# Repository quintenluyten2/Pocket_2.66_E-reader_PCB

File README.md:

# Pocket 2.66 — E-reader PCB

A compact e-reader PCB built around a 2.13"/2.66" e-ink display and the ESP32-C3FH4 microcontroller.

## Features

- **MCU:** ESP32-C3FH4 (RISC-V, 2.4 GHz Wi-Fi + BLE, 4 MB flash)
- **Display:** 2.13"/2.66" e-ink, connected via 24-pin FPC
- **Power:** USB-C input, single-cell Li-Po with GX4054 charger and BQ27220 fuel gauge
- **Storage:** micro-SD card slot
- **Connectivity:** On-board SMD 2.4 GHz antenna (Not yet matched to 35 Ohm)
- **Form factor:** 4-layer 1 mm PCB, min trace 0.12 mm, min via 0.3/0.4 mm (designed for JLCPCB)

## Repository contents

```
├── Pocket 2.66.kicad_sch       Schematic
├── Pocket 2.66.kicad_pcb       PCB layout
├── Pocket 2.66.kicad_pro       KiCad project file
├── Pocket 2.66.kicad_dru       Design rules
├── libs/lcsc/.                 Component Library
├── documentation/
│   ├── Pocket 2.66 BOM with MPN.csv   Schematic BOM
│   ├── Pocket 2.66 Interactive.html   Interactive PCB BOM
│   ├── PCB.stl
│   └── V0_schematic_review.pdf
└── production/
    ├── Pocket_2.66.zip         Gerber + drill files for fabrication
    ├── bom.csv                 JLCPCB BOM (for PCBA)
    ├── positions.csv           JLCPCB pick-and-place (for PCBA)
    └── netlist.ipc
```

## Additional parts
To make an E-reader, you need this PCB fully assembled, and:
- **Display** 24-pin 2.13"/2.66" Black/White E-ink display (e.g. Waveshare)
- **Battery** 803450 1500 mAh battery for 2.66" version or 802540 800 mAh battery for 2.13" version. Use 1.25 mm 2P Picoblade connector
- **Housing** 3D printing files coming soon

## Key components

| Ref | Part | Description |
|-----|------|-------------|
| U1 | ESP32-C3FH4 | Main MCU |
| U2 | LCK-TF-027H30008-WLG | Push-pull micro-SD slot |
| U3 | GX4054 | Li-Po charger |
| U4 | GS2019-33TR5 | 3.3 V LDO |
| U5 | BQ27220YZFR | Battery fuel gauge |
| U6 | SRV05-4-P-T7 | USB ESD protection |
| P1 | USB-TYPE-C-018 | USB-C connector |
| P3 | FPC-05F-24PH20 | 24-pin FPC for e-ink display |
| ANT2 | H2U38D1E1B0100 | 2.4 GHz SMD antenna |
| X1 | XL7EL89CLI-111YLC-40M | 40 MHz crystal |

## Opening the project

1. Open **KiCad 8** or later.
2. File → Open Project → select `Pocket 2.66.kicad_pro`.
3. The component library is self-contained in `libs/lcsc/`. The project's `fp-lib-table` and `sym-lib-table` already point to it, so no additional setup is needed.
4. Set the `KICAD_LCSC_3D_MODEL_DIR` path variable to `${KIPRJMOD}/libs/lcsc/3dmodels` for 3D models to appear (Preferences → Configure Paths).

## Production files

Ready-to-order Gerber files are in `production/Pocket_2.66.zip`. The BOM and pick-and-place files are formatted for JLCPCB PCBA.

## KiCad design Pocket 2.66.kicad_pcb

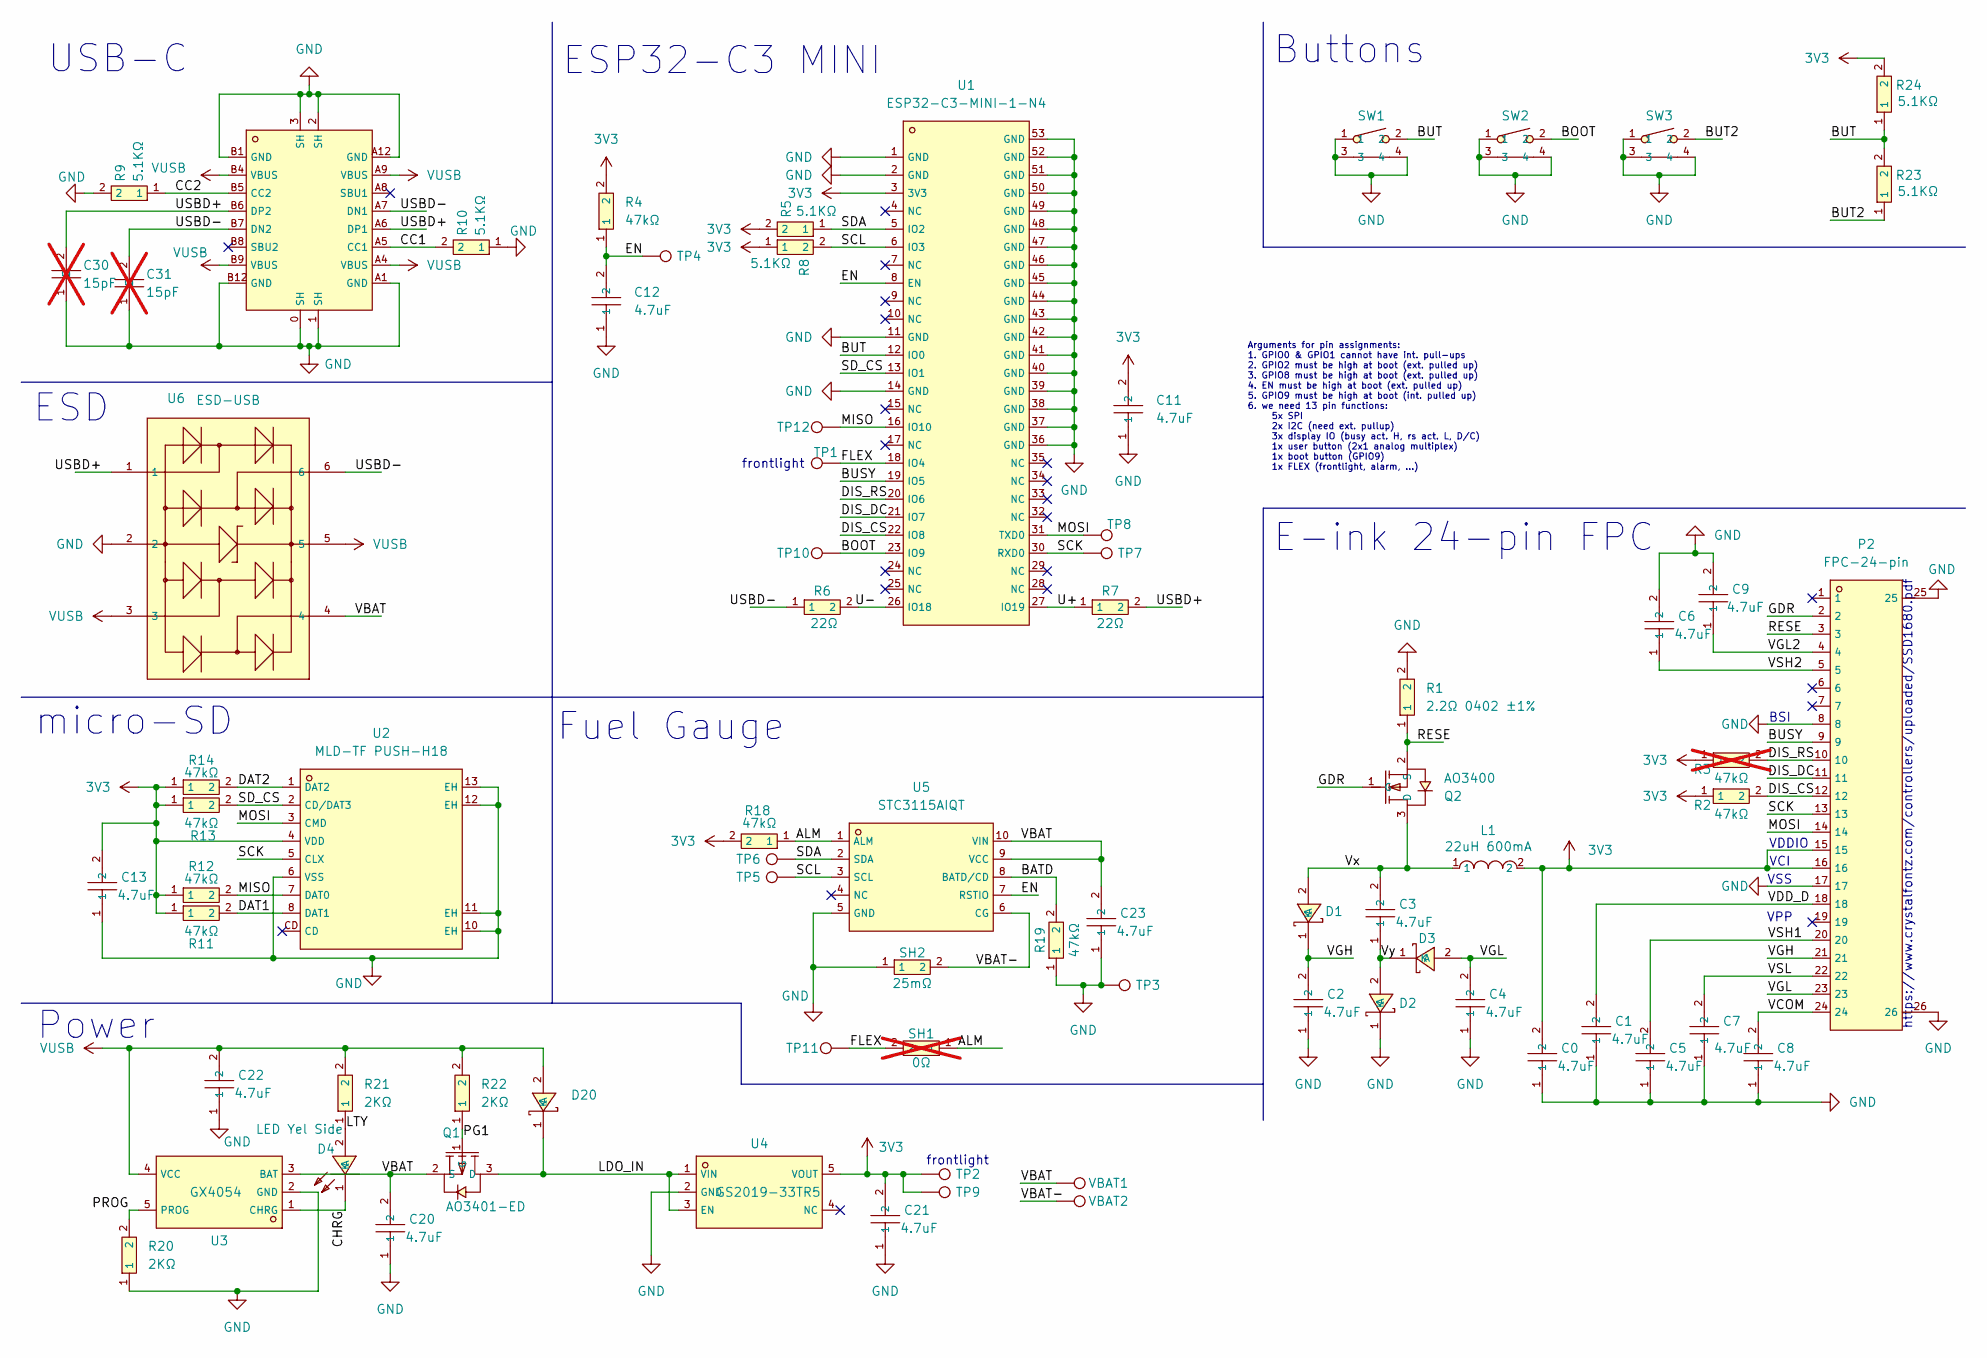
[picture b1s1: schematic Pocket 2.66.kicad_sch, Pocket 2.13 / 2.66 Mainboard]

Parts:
C0, C1, C2, C3, C4, C5, C6, C7, C8, C9, C11, C12, C13, C20, C21, C22, C23: 4.7uF; C0402; MPN CGA0402X5R475M250GT; LCSC C6119795
C30, C31: 15pF; C0402; MPN 0402CG150J500NT; LCSC C1548; not fitted
D1, D2, D3, D20: SD103AWS-L SOD-323; C191023_SOD-323_L1_8-W1_3-LS2_5-RD; MPN SD103AWS-L; LCSC C41376466
D4: LED Yel Side; C52675985_LED_Side; MPN CT-1706UYC-P11; LCSC C52675985
L1: 22uH 600mA; C48689518_L1008; MPN SRTC.252010.YB220MT00; LCSC C48689518
P1: TYPE-C 16P CB1.6 073; C2906290_USB-C-SMD_SHOU_TYPE-C-16P-CB1_6; MPN TYPE-C 16P CB1.6 073; LCSC C2906290
P2: FPC-24-pin; C324726_FFC-SMD_24P-P0_50_FH34SRJ-24S-0_5SH; MPN FH34SRJ-24S-0.5SH(50); LCSC C324726
Q1: AO3401-ED; SOT23-3; MPN AO3401-ED; LCSC C4748724
Q2: AO3400; SOT-23-L; MPN AO3400; LCSC C20634976
R1: 2.2Ω 0402 ±1%; R0402; MPN FRC0402F2R20TS; LCSC C2909330
R2, R4, R11, R12, R13, R14, R18, R19: 47kΩ; R0402; MPN FRC0402F4702TS; LCSC C2906872
R3: 47kΩ; R0402; MPN FRC0402F4702TS; LCSC C2906872; not fitted
R5, R8, R9, R10, R23, R24: 5.1KΩ; R0402; MPN 0402WGF5101TCE; LCSC C25905
R6, R7: 22Ω; R0402; MPN RC0402FR-0722RL; LCSC C114765
R20, R21, R22: 2KΩ; R0402; MPN 0402WGF2001TCE; LCSC C4109
SH1: 0Ω; R0402; not fitted
SH2: 25mΩ; R0603; MPN RL0603FR-070R025L; LCSC C859739
SW1, SW2, SW3: TS-24CA-S16; C42420265_SW-SMD_L4_7-W3_5-P3_35-EH; MPN TS-24CA-S16; LCSC C42420258
TP1, TP2: TestPoint; TestPoint_Pad_D1.5mm
TP3, TP4, TP5, TP6, TP7, TP8, TP9, TP10, TP11, TP12: TestPoint; TestPoint_Pad_D1.0mm
U1: ESP32-C3-MINI-1-N4; C2838502_WIFIM-SMD_ESP32-C3-MINI-1; LCSC C2838502
U2: MLD-TF PUSH-H18; C52750848_SD-SMD_MLD-TF-PUSH-H18; LCSC C52750848
U3: GX4054; SOT-23-5; MPN GX4054; LCSC C5259235
U4: GS2019-33TR5; SOT-23-5; MPN GS2019-33TR5; LCSC C41419378
U5: STC3115AIQT; C2688637_DFN-10_L3_0-W2_0-P0_50-BL; MPN STC3115AIQT; LCSC C2688637
U6: ESD-USB; C85364_SOT-23-6_L2_9-W1_6-P0_95-LS2_8-BR; MPN SRV05-4-P-T7; LCSC C85364
VBAT1, VBAT2: TestPoint; TestPoint_Pad_D1.0mm

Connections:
3V3: C0.2, C11.2, C13.2, C21.2, L1.2, P2.15, P2.16, R2.1, R3.1, R4.2, R5.2, R8.1, R11.1, R12.1, R13.1, R14.1, R18.2, R24.2, TP2.1 (1_1), TP9.1 (1_1), U1.3 (3V3), U2.4 (VDD), U4.5 (VOUT)
/ALM: R18.1, SH1.1, U5.1 (ALM)
/BATD: R19.2, U5.8 (BATD/CD)
/BOOT: SW2.2, TP10.1 (1_1), U1.23 (IO9)
/BUSY: P2.9, U1.19 (IO5)
/BUT: R23.2, R24.1, SW1.2, U1.12 (IO0)
/BUT2: R23.1, SW3.2
/CC1: P1.A5 (CC1), R10.2
/CC2: P1.B5 (CC2), R9.1
/CHRG: D4.1 (K), U3.1 (CHRG)
/DAT1: R11.2, U2.8 (DAT1)
/DAT2: R14.2, U2.1 (DAT2)
/DIS_CS: P2.12, R2.2, U1.22 (IO8)
/DIS_DC: P2.11, U1.21 (IO7)
/DIS_RS: P2.10, R3.2, U1.20 (IO6)
/EN: C12.2, R4.1, TP4.1 (1_1), U1.8 (EN), U5.7 (RSTIO)
/FLEX: SH1.2, TP1.1 (1_1), TP11.1 (1_1), U1.18 (IO4)
/GDR: P2.2, Q2.1 (G)
/LDO_IN: D20.1 (K), Q1.3 (D), U4.1 (VIN), U4.3 (EN)
/LTY: D4.2 (A), R21.1
/MISO: R12.2, TP12.1 (1_1), U1.16 (IO10), U2.7 (DAT0)
/MOSI: P2.14, TP8.1 (1_1), U1.31 (TXD0), U2.3 (CMD)
/PG1: Q1.1 (G), R22.1
/PROG: R20.2, U3.5 (PROG)
/RESE: P2.3, Q2.2 (S), R1.1
/SCK: P2.13, TP7.1 (1_1), U1.30 (RXD0), U2.5 (CLX)
/SCL: R8.2, TP5.1 (1_1), U1.6 (IO3), U5.3 (SCL)
/SDA: R5.1, TP6.1 (1_1), U1.5 (IO2), U5.2 (SDA)
/SD_CS: R13.2, U1.13 (IO1), U2.2 (CD/DAT3)
/U+: R7.1, U1.27 (IO19)
/U-: R6.2, U1.26 (IO18)
/USBD+: C30.2, P1.A6 (DP1), P1.B6 (DP2), R7.2, U6.1
/USBD-: C31.2, P1.A7 (DN1), P1.B7 (DN2), R6.1, U6.6
/VBAT: C20.2, C23.2, Q1.2 (S), U3.3 (BAT), U5.9 (VCC), U5.10 (VIN), U6.4, VBAT1.1 (1_1)
/VBAT-: SH2.2, U5.6 (CG), VBAT2.1 (1_1)
/VCOM: C8.2, P2.24
/VDD_D: C1.2, P2.18
/VGH: C2.2, D1.1 (K), P2.21
/VGL: C4.2, D3.2 (A), P2.23
/VGL2: C9.1, P2.4
/VSH1: C5.2, P2.20
/VSH2: C6.1, P2.5
/VSL: C7.2, P2.22
/Vx: C3.2, D1.2 (A), L1.1, Q2.3 (D)
/Vy: C3.1, D2.2 (A), D3.1 (K)
GND: C0.1, C1.1, C2.1, C4.1, C5.1, C6.2, C7.1, C8.1, C9.2, C11.1, C12.1, C13.1, C20.1, C21.1, C22.1, C23.1, C30.1, C31.1, D2.1 (K), P1.0 (SH), P1.1 (SH), P1.2 (SH), P1.3 (SH), P1.A1 (GND), P1.A12 (GND), P1.B1 (GND), P1.B12 (GND), P2.8, P2.17, P2.25, P2.26, R1.2, R9.2, R10.1, R19.1, R20.1, SH2.1, SW1.1, SW1.3, SW1.4, SW2.1, SW2.3, SW2.4, SW3.1, SW3.3, SW3.4, TP3.1 (1_1), U1.1 (GND), U1.2 (GND), U1.11 (GND), U1.14 (GND), U1.36 (GND), U1.37 (GND), U1.38 (GND), U1.39 (GND), U1.40 (GND), U1.41 (GND), U1.42 (GND), U1.43 (GND), U1.44 (GND), U1.45 (GND), U1.46 (GND), U1.47 (GND), U1.48 (GND), U1.49 (GND), U1.50 (GND), U1.51 (GND), U1.52 (GND), U1.53 (GND), U2.6 (VSS), U2.10 (EH), U2.11 (EH), U2.12 (EH), U2.13 (EH), U3.2 (GND), U4.2 (GND), U5.5 (GND), U6.2
VUSB: C22.2, D20.2 (A), P1.A4 (VBUS), P1.A9 (VBUS), P1.B4 (VBUS), P1.B9 (VBUS), R21.2, R22.2, U3.4 (VCC), U6.3, U6.5

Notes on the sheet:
Power
https://www.crystalfontz.com/controllers/uploaded/SSD1680.pdf
BSI
VCI
VPP
frontlight
Buttons
micro-SD
VSS
Arguments for pin assignments: 1. GPIO0 & GPIO1 cannot have int. pull-ups 2. GPIO2 must be high at boot (ext. pulled up) 3. GPIO8 must be high at boot (ext. pulled up) 4. EN must be high at boot (ext. pulled up) 5. GPIO9 must be high at boot (int. pulled up) 6. we need 13 pin functions: 5x SPI 2x I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
USB-C
ESP32-C3 MINI
E-ink 24-pin FPC
Fuel Gauge
ESD
VDDIO

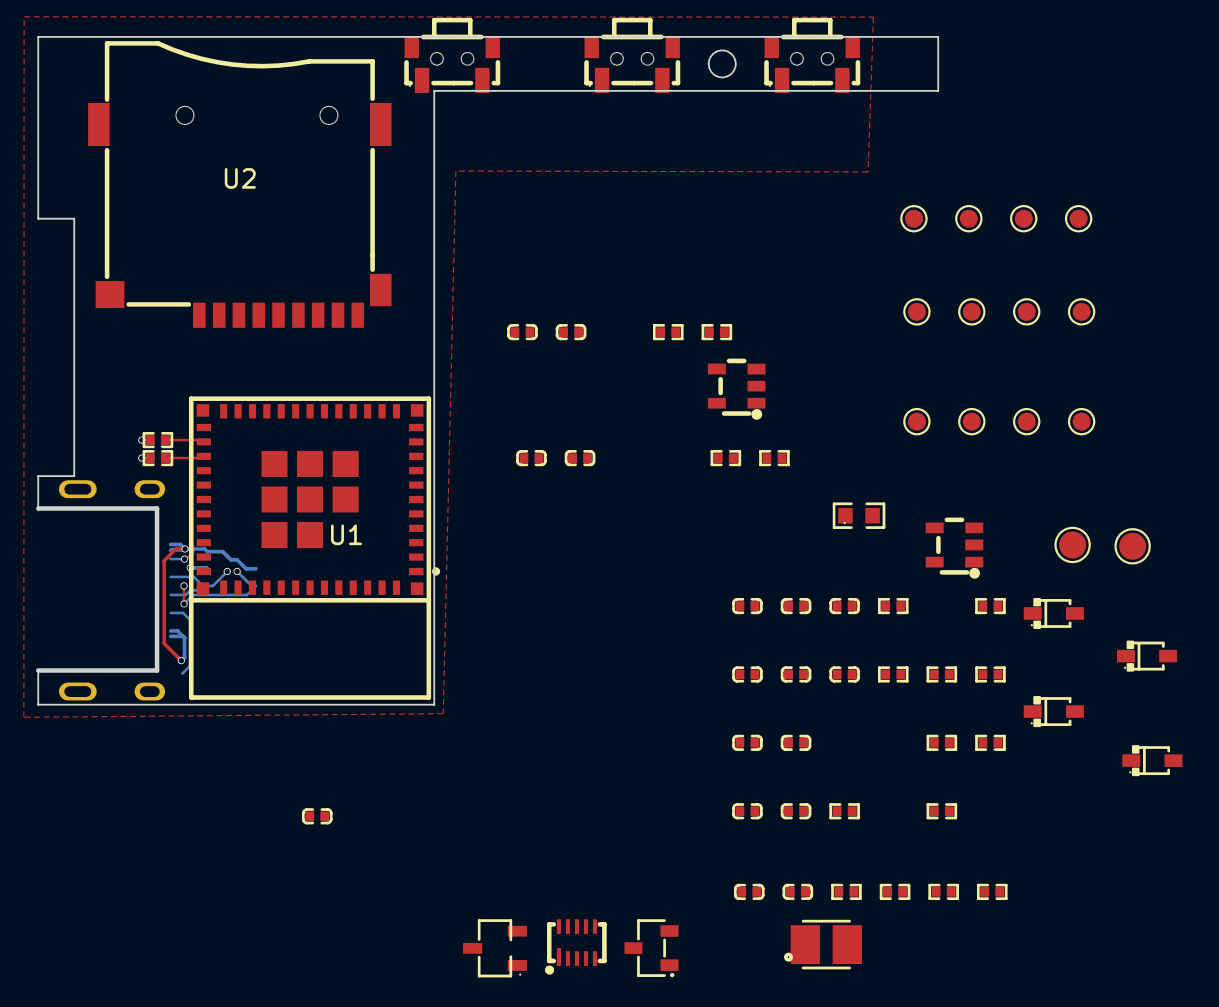
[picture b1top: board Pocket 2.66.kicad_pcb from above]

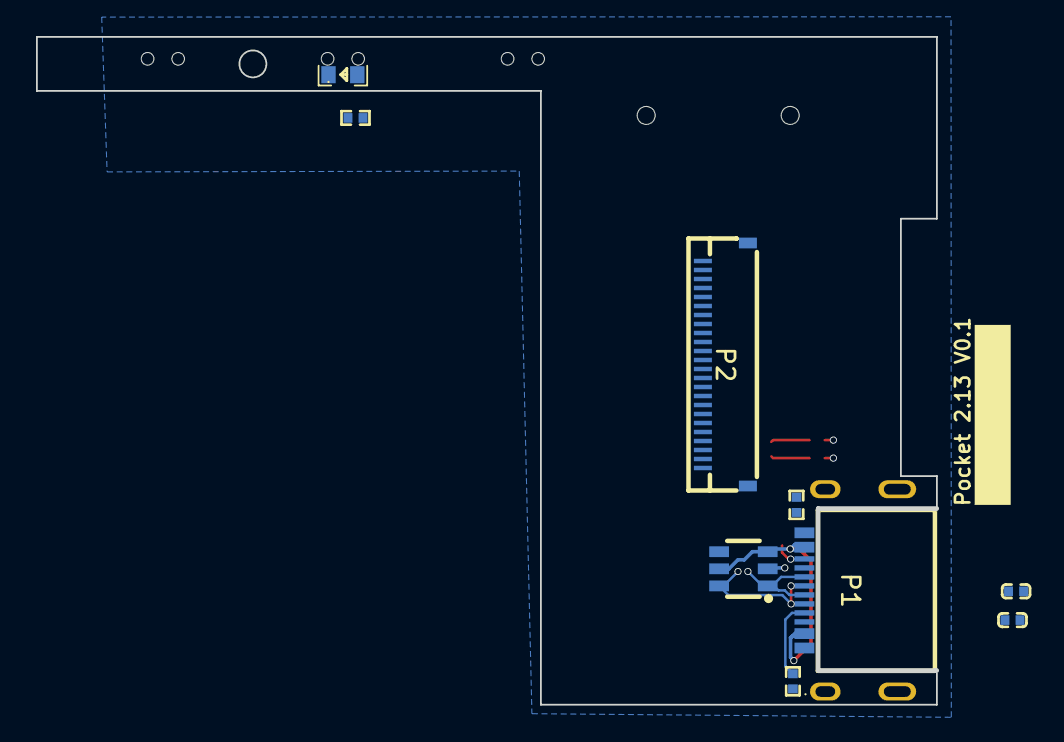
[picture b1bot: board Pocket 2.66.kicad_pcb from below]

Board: 4 copper layers, 50.0 x 37.1 mm, 75 parts (9 on the bottom side), 47 nets.

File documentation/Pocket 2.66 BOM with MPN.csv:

"Reference","Qty","Value","Manufacturer","LCSC","JLC Type","MPN"
"C0,C1,C2,C3,C4,C5,C6,C7,C8,C9,C11,C12,C13,C20,C21,C22,C23","17","4.7uF","HRE","C6119795","Extended","CGA0402X5R475M250GT"
"D1,D2,D3,D20","4","SD103AWS-L SOD-323","PIELENST","C41376466","Extended","SD103AWS-L"
"D4","1","RED","Hubei KENTO Elec","C2286","","KT-0603R"
"L1","1","22uH 600mA","SOREDE","C48689518","","SRTC.252010.YB220MT00"
"P1","1","USB-TYPE-C-018","DEALON","C2927038","","USB-TYPE-C-018"
"P3","1","FPC-05F-24PH20","XUNPU","C2856805","","FPC-05F-24PH20"
"P4","1","HX-1.25-2AWB","hanxia","C52016406","","HX-1.25-2AWB"
"Q1","1","AO3401-ED","HXY MOSFET","C4748724","Extended","AO3401-ED"
"Q2","1","AO3400","FOSAN","C20634976","Extended","AO3400"
"R1","1","2.2Ω 0402 ±1%","FOJAN","C2909330","Extended","FRC0402F2R20TS"
"R2,R4,R11,R12,R13,R14,R18,R19","8","47kΩ","FOJAN","C2906872","Extended","FRC0402F4702TS"
"R5,R8,R9,R10,R23,R24","6","5.1KΩ","UNI-ROYAL","C25905","","0402WGF5101TCE"
"R6,R7","2","22Ω","Yageo","C114765","Extended","RC0402FR-0722RL"
"R20,R21,R22","3","2KΩ","UNI-ROYAL","C4109","","0402WGF2001TCE"
"SH2","1","25mΩ","YAGEO","C859739","Extended","RL0603FR-070R025L"
"SW1,SW2,SW3","3","TS-24CA-S16","JXTCONN","C42420258","","TS-24CA-S16"
"U1","1","ESP32-C3-MINI-1-N4","ESPRESSIF(乐鑫)","C2838502","",""
"U2","1","LCK-TF-027H37508-WLG","LCKELEC","C50380694","Extended","LCK-TF-027H37508-WLG"
"U3","1","GX4054","GUOXIN JIAPIN SEMICONDUCTOR","C5259235","","GX4054"
"U4","1","GS2019-33TR5","Gainsil","C41419378","","GS2019-33TR5"
"U5","1","STC3115AIQT","ST Microelectronics","C2688637","","STC3115AIQT"
"U6","1","ESD-USB","PROTEK","C85364","","SRV05-4-P-T7"

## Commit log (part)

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2026-05-18 Update RF on schematic and BOM details
2026-05-18 Move 2R2 basic part to top side
2026-05-18 remove vias from serial no. area
2026-05-18 Add PCB images to README and update gitignore
2026-05-19 Add extra test pads
2026-05-19 Add second RF shunt (DNP) for extra matching flexibility
2026-05-20 Remove floating traces
2026-05-23 Add 7 new library entries with MPN, Manufacturer, and LCSC Type
    - SOT-23-L generic footprint (clone of SOT23-3)
    - AO3400 NMOS (C20634976, FOSAN) → SOT-23-L
    - AO3401-ED PMOS (C4748724, HXY MOSFET) → SOT23-3
    - LCK-TF-027H37508-WLG SD slot (C50380694, LCKELEC) → C50380692 footprint
    - 2.2Ω 0402 ±1% (C2909330, FOJAN)
    - 47kΩ 0402 ±1% (C2906872, FOJAN)
2026-05-23 Remove incorrect SOT-23-L footprint (clone of SOT23-3)
2026-05-23 Add SOT-23-L footprint and 3D models from C20634976
2026-05-23 Add SD103AWS-L symbol (C41376466) and rename LCSC Type to JLC Type
    - New symbol SD103AWS-L SOD-323 (C41376466, PIELENST) with same
    SOD-323 footprint/pinout as C191023, JLC Type: Extended
    - Rename all "LCSC Type" properties to "JLC Type" in 5 symbol files
    and 77 occurrences in the schematic
2026-05-23 Schematics for ESP32-C3 mini module
2026-06-19 Test code for most features of this E-reader
2026-06-19 Update test script
